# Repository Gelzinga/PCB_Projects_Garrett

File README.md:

# PCB_Projects_Garrett
Repository of PCB designs

This repository contains some of my recent PCB designs, namely an active filtering op-amp circuit for a laser tag receiver, an IOT board with onboard buck converter and external hardware support, and a low-power bluetooth remote . All designs have been done in KiCad.

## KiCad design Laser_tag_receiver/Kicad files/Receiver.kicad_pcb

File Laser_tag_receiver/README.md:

###### THIS IS THE READ ME FOR THE RECEIVER BOARD #######

This board is a receiver for a laser tag project. The circuit is built with two op-amps with active filtering. The low pass filters are implimented using a series capacitor and resistor, and the high pass filters 
with the Gain bandwidth product property of the OP-AMP. The circuit attenuates high and low noise frequencies and provides around 160 dB of gain to the desired current domain signal genererated through the photdiode. Expected noise frequencies of 100 Hz and 10k hz. Circuit provides more than enough attenuation for noise signals, around 60 dB. 

Design Choices 
1. Capacitors were placed close to the power rails in order to achieve effective stabilization of power supply. 
2. Additional low pass filter was placed on power supply to eliminate higher frequency noise directly from the power.
3. Gain bandwidth property of opamp was used for high frequency noise attenuation to reduce compenents/complexity/poles of the circuit.
4. Gain around 160 dB in order to provide a useful signal. Attenuation of expected noise signals around 60 dB down. Bode plot is included in the PCB folder.
5. Ground was made a plane to reduce noise
6. Two inverting OP-AMPS were used. More OP-AMPS could've been used to increase gain, but for lower complexity and cost just two were used. 

Debugging Process
1. Major challenge was fitting all of the components in the board. Several vias had to be used
2. LT Spice schematic was used to verify appropriate attenuation of signals.
3. Included hardware support for extra filters for more attenuation if needed. Pins were used that can be bypassed with header caps.

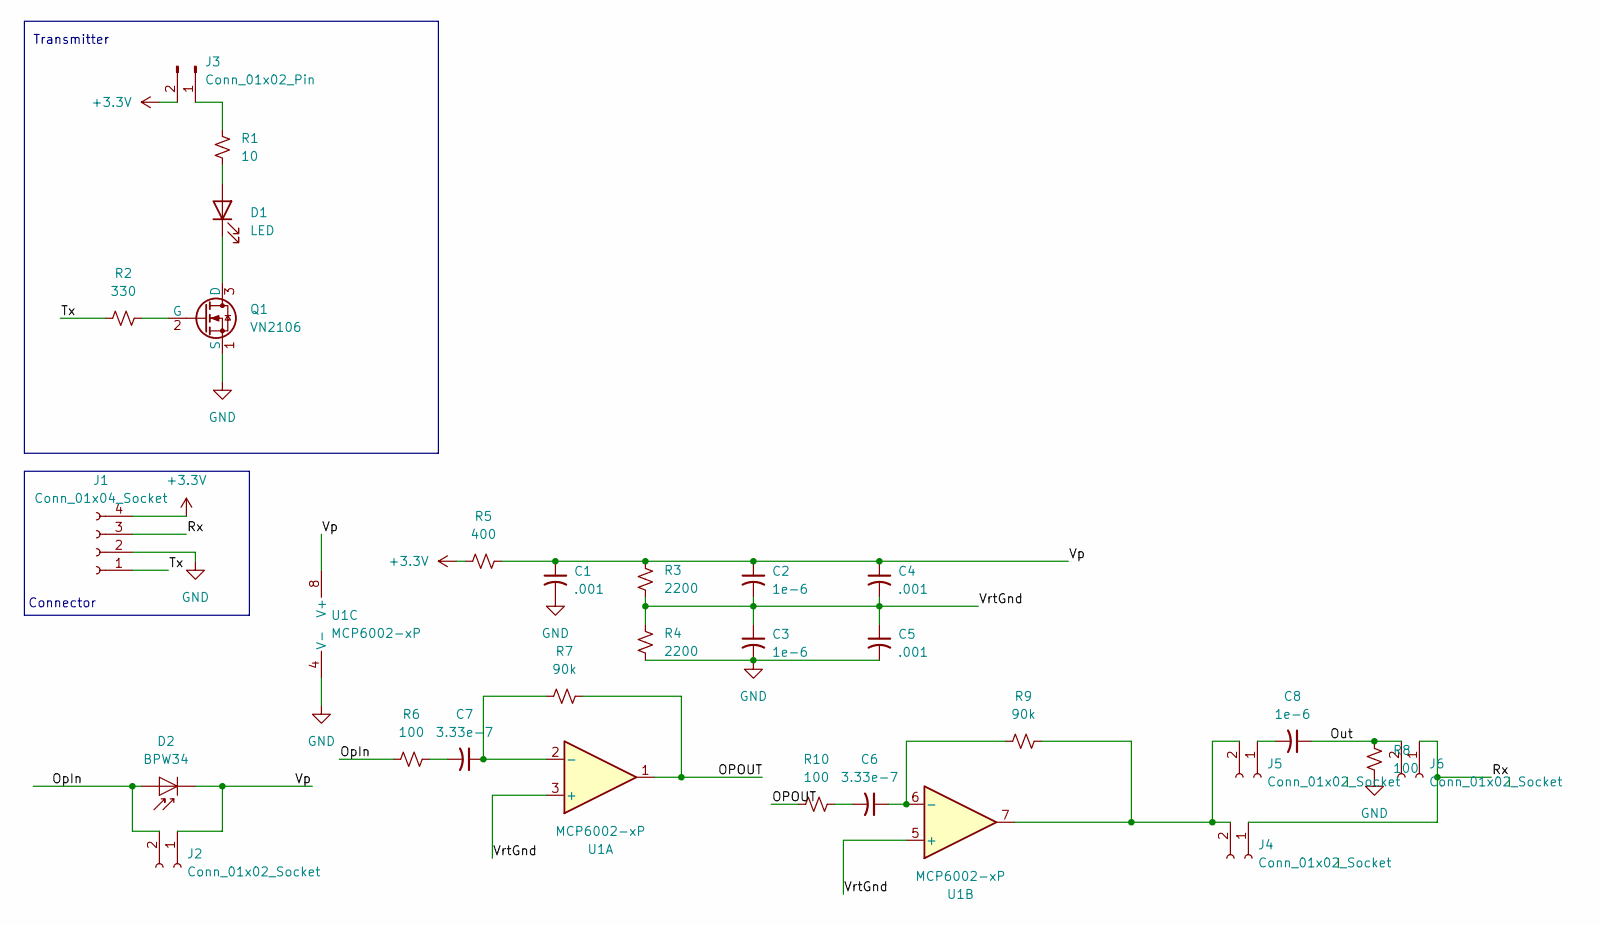
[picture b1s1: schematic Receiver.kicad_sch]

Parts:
C1, C4, C5: .001; CP_Radial_D10.0mm_P5.00mm
C2, C3, C8: 1e-6; C_Disc_D10.0mm_W2.5mm_P5.00mm
C6, C7: 3.33e-7; C_Disc_D10.0mm_W2.5mm_P5.00mm
D1: LED; LED_D3.0mm
D2: BPW34; Osram_DIL2_4.3x4.65mm_P5.08mm
J1: Conn_01x04_Socket; PinSocket_1x04_P2.54mm_Vertical
J2, J4, J5, J6: Conn_01x02_Socket; JST_PH_B2B-PH-K_1x02_P2.00mm_Vertical
J3: Conn_01x02_Pin; PinHeader_1x02_P2.54mm_Vertical
Q1: VN2106; TO-92L_Inline
R1: 10; R_Axial_DIN0207_L6.3mm_D2.5mm_P7.62mm_Horizontal
R2: 330; R_Axial_DIN0207_L6.3mm_D2.5mm_P7.62mm_Horizontal
R3, R4: 2200; R_Axial_DIN0207_L6.3mm_D2.5mm_P7.62mm_Horizontal
R5: 400; R_Axial_DIN0207_L6.3mm_D2.5mm_P7.62mm_Horizontal
R6, R8, R10: 100; R_Axial_DIN0207_L6.3mm_D2.5mm_P7.62mm_Horizontal
R7, R9: 90k; R_Axial_DIN0207_L6.3mm_D2.5mm_P7.62mm_Horizontal
U1: MCP6002-xP; DIP-8_W7.62mm

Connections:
+3.3V: J1.4, J3.2, R5.1
/OPOUT: R7.2, R10.1, U1.1
/OpIn: D2.2 (A), J2.2, R6.1
/Out: C8.1, J6.2, R8.2
/Rx: J1.3, J4.1, J6.1
/Tx: J1.1, R2.1
/Vp: C1.1, C2.1, C4.1, D2.1 (K), J2.1, R3.1, R5.2, U1.8 (V+)
/VrtGnd: C2.2, C3.1, C4.2, C5.1, R3.2, R4.1, U1.3 (+), U1.5 (+)
GND: C1.2, C3.2, C5.2, J1.2, Q1.1 (S), R4.2, R8.1, U1.4 (V-)
unnamed: C6.2, R10.2
unnamed: C7.2, R6.2
unnamed: D1.2 (A), R1.2
unnamed: D1.1 (K), Q1.3 (D)
unnamed: J3.1, R1.1
unnamed: J4.2, J5.2, R9.2, U1.7
unnamed: C8.2, J5.1
unnamed: Q1.2 (G), R2.2
unnamed: C7.1, R7.1, U1.2 (-)
unnamed: C6.1, R9.1, U1.6 (-)

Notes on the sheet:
Transmitter
Connector

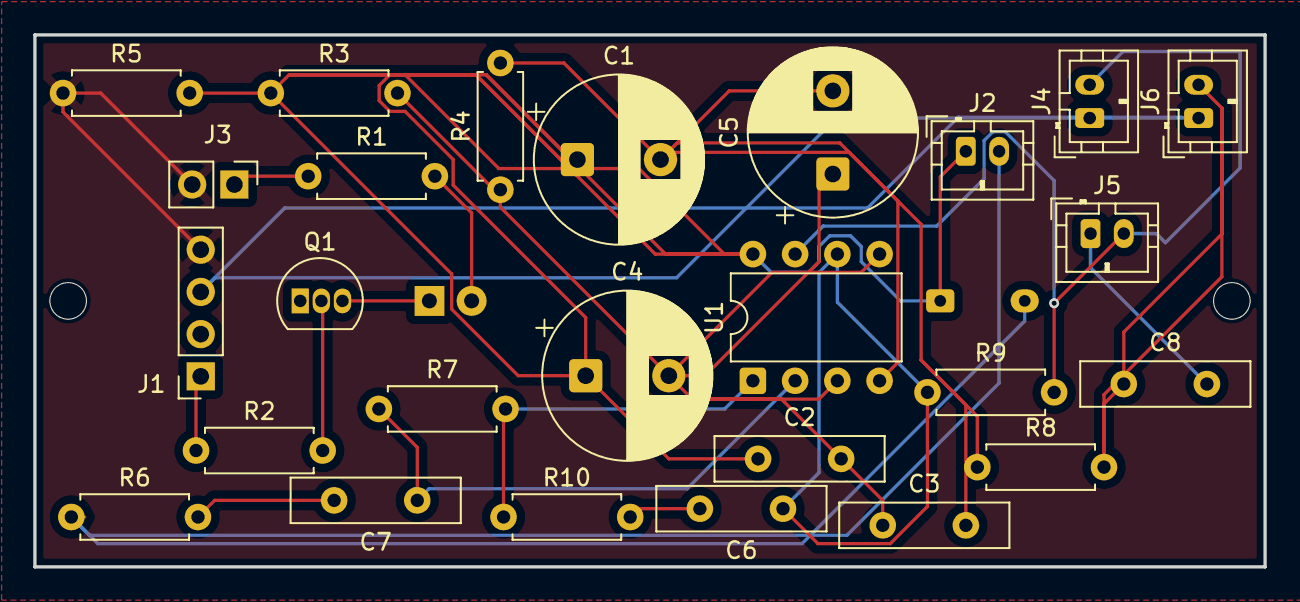
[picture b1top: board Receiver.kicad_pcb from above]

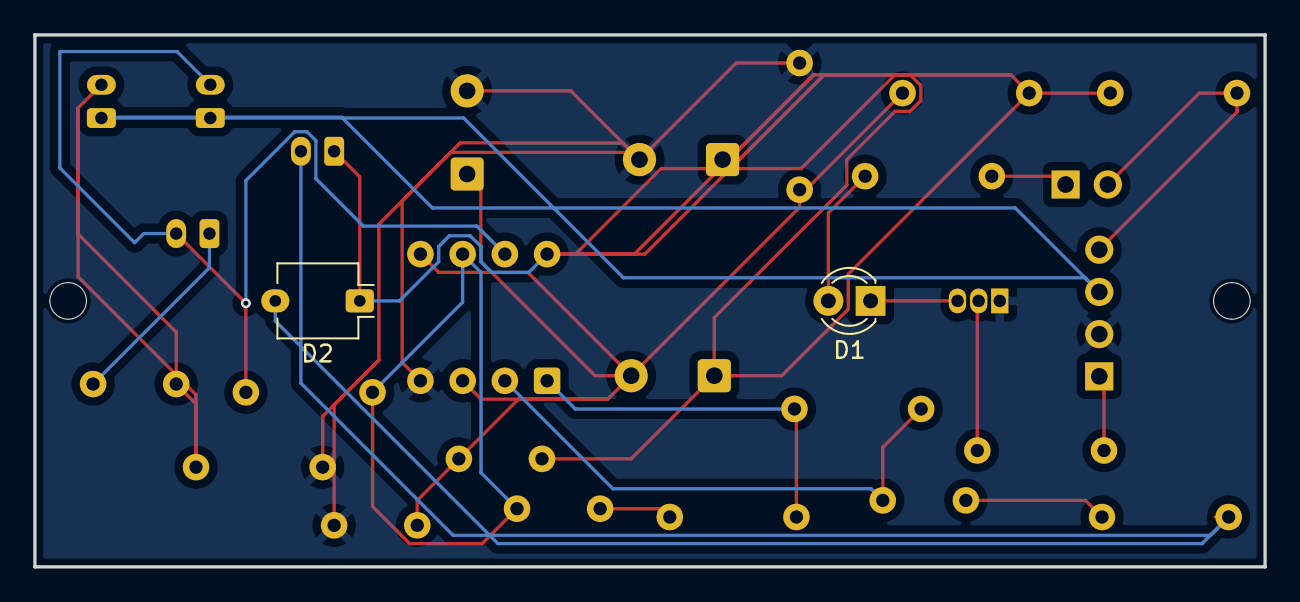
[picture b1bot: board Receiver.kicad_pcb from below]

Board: 2 copper layers, 74.0 x 32.0 mm, 28 parts (2 on the bottom side), 19 nets.

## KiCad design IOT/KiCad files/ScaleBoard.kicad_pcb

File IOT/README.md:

#### THIS IS THE READ ME FILE FOR THE IOT BOARD #####

In this folder you will find 

- Schematics 
- PCB pictures 
- KiCad files

Motivation for this board: 
This board is designed as a custom IOT device to read a digital output from a load cell ( Analog values already converted using off-board PCB) and display the value on a screen, 
indicating that more or less ingredients from the recipe sent from phone to the esp32 need to be included. Will make cooking easier and more convenient. 

Design Decisions: 
1. Multiple decoupling capacitors, each with different values to block low high, low and midband frequency noise. Decoupling capacitors were placed at several stages, but most noteably the raw input from the power supply.
2. Decoupling capacitors were placed close to the power/ground pins that they are connected to in order to further reduce noise (low noise is an absolute esssential, as the power supply must be  extremely stable
to get accurate readings from the load cell).
3. Buck converter was implimented to convert the 5v to 3.3v. The converter holds the voltage at .8 V at FB pin, so a resistor divider with high value resistors (to reduce power loss) was used. Values of 312.5k  and 100k achieve necessary 3.3v.
5. Ground was implimented as a plane to reduce potential sources of noise
6. Hardware support for a button was added, using an external pull up resistor for clarity as well as clean design. Large R values to reduce current power consumption 
7. Hardware support for SPI screen was included as well, to display the scale readings/progress.

Debugging process: 
1. Appropriate spacing to ensure proximity of capacitors to rails while still allowing for reasonable space for soldering and placement was a major problem.It required moving traces and footprints around, implimenting vias and using traces on both sides.
2. ESP 32 S3 footprint straight from the library had some vias that were .2 mm, changed to .3 mm for fabrication plausability/compatibility
3. Buck converter comes as an SMD, so this complicated things as either vias had to be made or priority for top-side traces.
4. Resistors were changed from SMD to THT for prototyping and less complexity/crowded traces on the front side. SMD technology to be explored in later iterations.

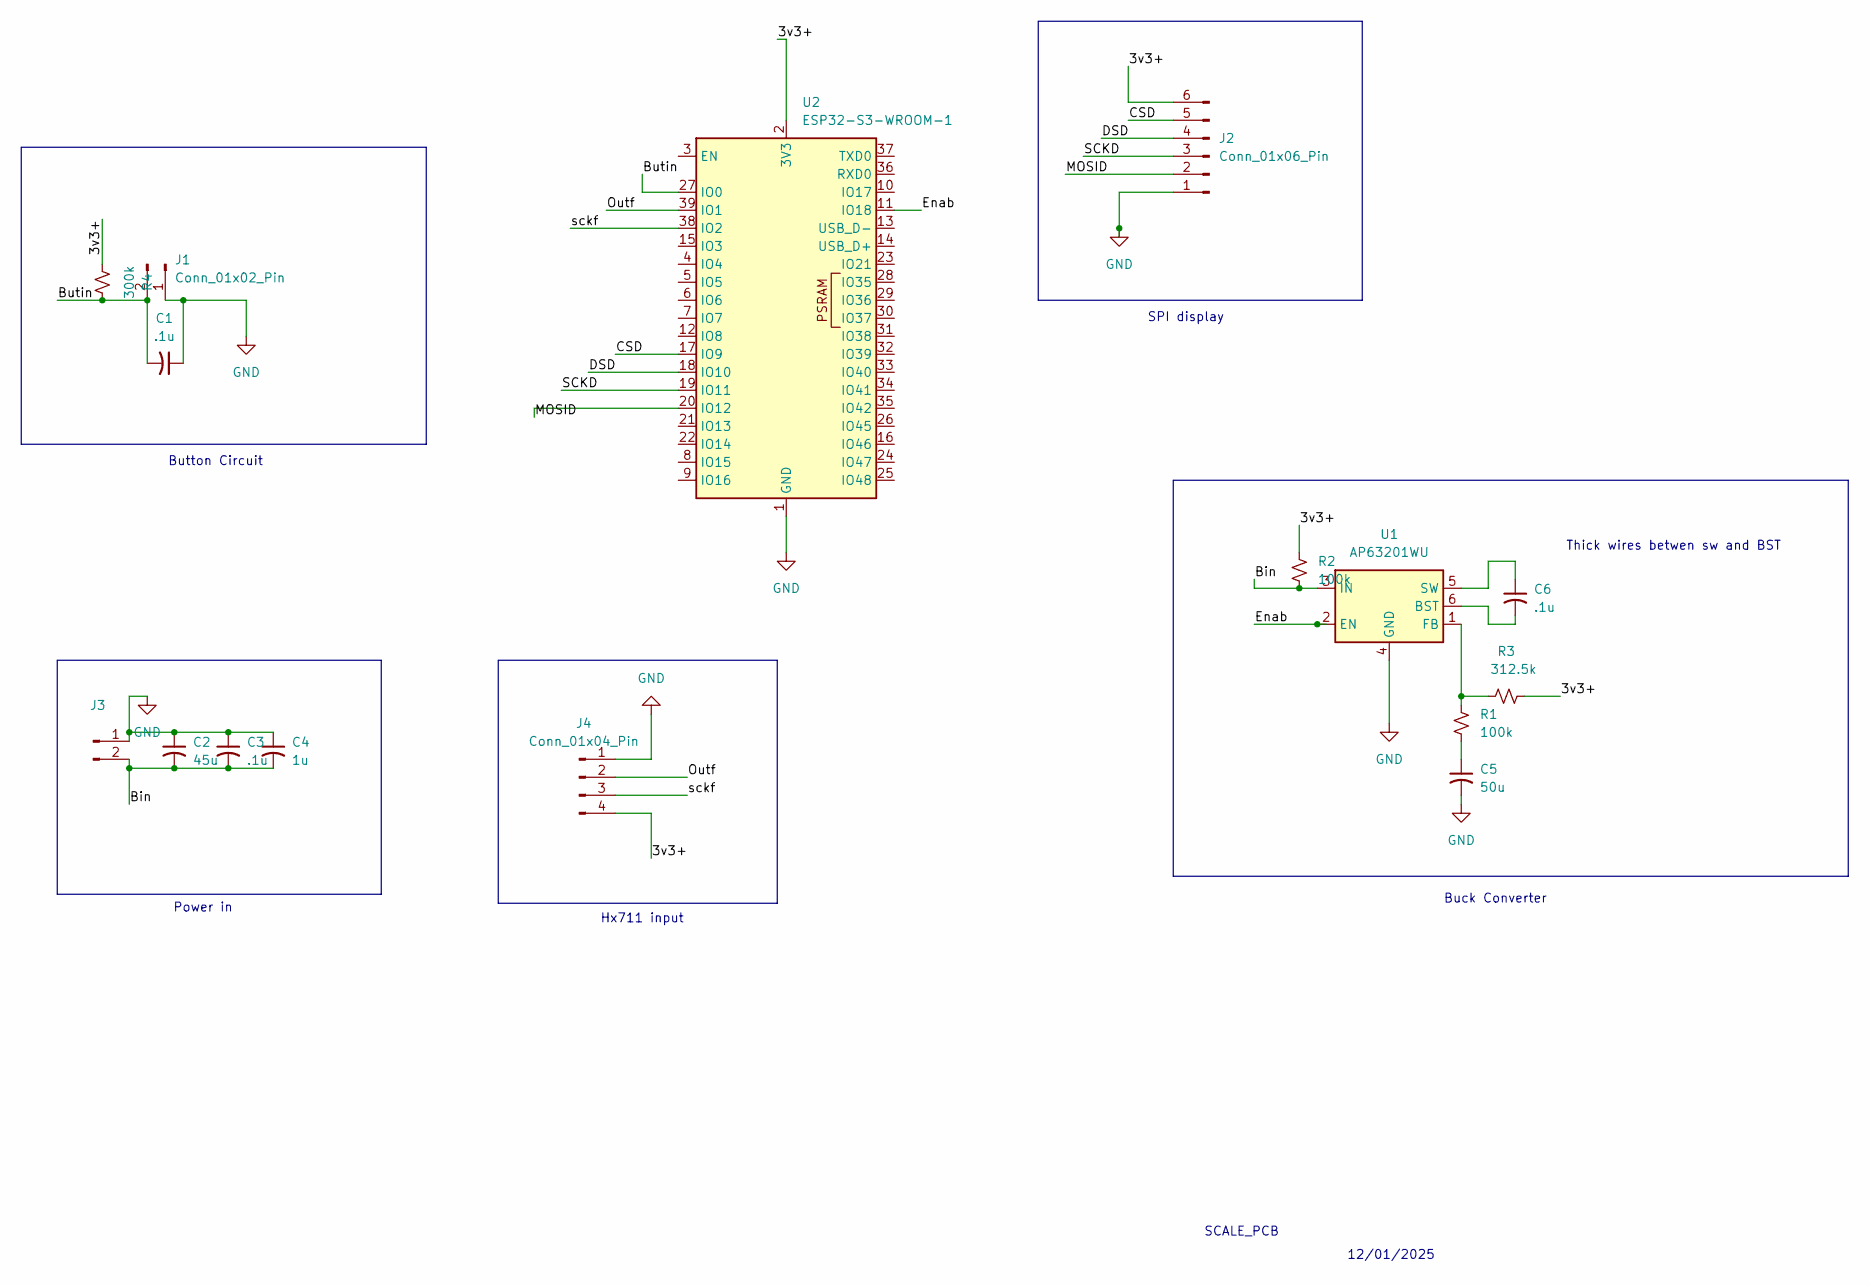
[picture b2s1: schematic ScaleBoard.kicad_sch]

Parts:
C1, C3, C6: .1u; C_Disc_D5.1mm_W3.2mm_P5.00mm
C2: 45u; C_Disc_D5.1mm_W3.2mm_P5.00mm
C4: 1u; C_Disc_D5.1mm_W3.2mm_P5.00mm
C5: 50u; C_Disc_D5.1mm_W3.2mm_P5.00mm
J1, J3: Conn_01x02_Pin; PinHeader_1x02_P2.54mm_Vertical
J2: Conn_01x06_Pin; PinHeader_1x06_P2.54mm_Vertical
J4: Conn_01x04_Pin; PinHeader_1x04_P2.54mm_Vertical
R1, R2: 100k; R_Axial_DIN0207_L6.3mm_D2.5mm_P7.62mm_Horizontal
R3: 312.5k; R_Axial_DIN0207_L6.3mm_D2.5mm_P7.62mm_Horizontal
R4: 300k; R_Axial_DIN0207_L6.3mm_D2.5mm_P7.62mm_Horizontal
U1: AP63201WU; TSOT-23-6
U2: ESP32-S3-WROOM-1

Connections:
/3v3+: J2.6, J4.4, R2.1, R3.2, R4.1, U2.2 (3V3)
/Bin: C2.2, C3.2, C4.2, J3.2, R2.2, U1.3 (IN)
/Butin: C1.2, J1.2, R4.2, U2.27 (IO0)
/CSD: J2.5, U2.17 (IO9)
/DSD: J2.4, U2.18 (IO10)
/Enab: U1.2 (EN), U2.11 (IO18)
/MOSID: J2.2, U2.20 (IO12)
/Outf: J4.2, U2.39 (IO1)
/SCKD: J2.3, U2.19 (IO11)
/sckf: J4.3, U2.38 (IO2)
GND: C1.1, C2.1, C3.1, C4.1, C5.2, J1.1, J2.1, J3.1, J4.1, U1.4 (GND), U2.1 (GND), U2.40 (GND), U2.41 (GND)
unnamed: C5.1, R1.2
unnamed: C6.2, U1.6 (BST)
unnamed: R1.1, R3.1, U1.1 (FB)
unnamed: C6.1, U1.5 (SW)

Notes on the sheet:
12/01/2025
SPI display
Buck Converter
SCALE_PCB
Button Circuit
Thick wires betwen sw and BST
Power in
Hx711 input

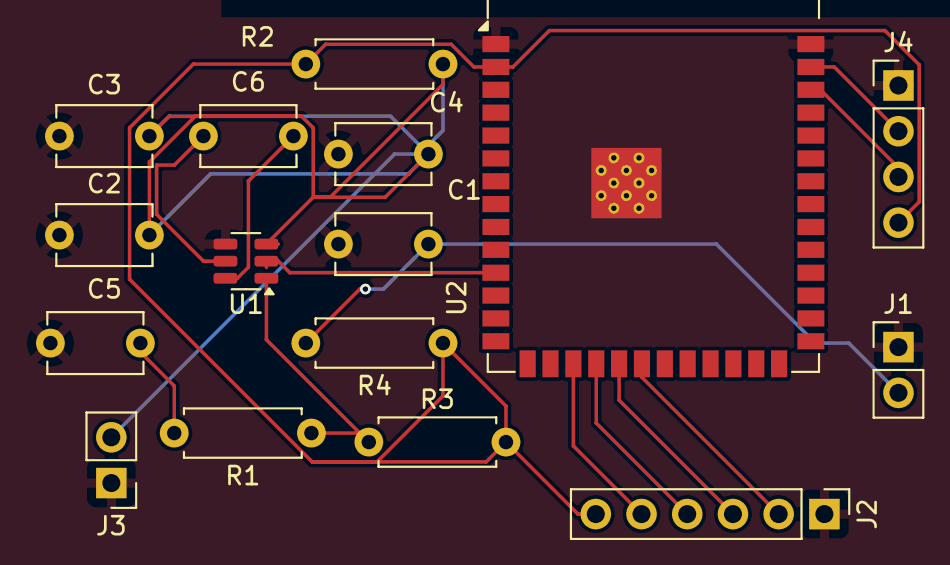
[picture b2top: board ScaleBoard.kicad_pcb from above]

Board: 2 copper layers, 16 parts (0 on the bottom side), 15 nets.

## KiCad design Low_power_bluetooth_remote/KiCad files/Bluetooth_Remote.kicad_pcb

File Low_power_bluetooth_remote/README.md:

# Bluetooth Remote Controller (ESP32)

## Overview
This project is a **low-power Bluetooth remote controller** using an ESP32-S3 MCU.  
It supports multiple buttons for controlling music playback and other Bluetooth HID commands. The design focuses on **low sleep current, clean grounding, proper power design, and reliable input handling**.  

The goal is not just a working remote, but a **portfolio-quality PCB demonstrating best practices in embedded hardware design**.

---

## Features

- ESP32-S3-WROOM-1 MCU (supports Bluetooth Low Energy)
- Up to 4 buttons (Bin1–Bin4)
- USB-C for power and programming
- Low dropout regulator for 3.3 V power supply
- Decoupling capacitors near power pins
- RC filters for buttons to suppress EMI
- Designed for low sleep current (<10 µA target)
- Clean ground plane with controlled high-current loops
- Optional LED indicators for button press feedback
- 2-layer PCB, designed for manufacturability

---

## Design Decisions

### 1. Power Design
- **Input:** USB 5 V  
- **Voltage Regulation:** AP63201 buck converter provides 3.3 V for MCU and peripherals.  
- **Decoupling:** 0.1–1 µF capacitors placed directly at power pins to reduce switching noise.  
- **Battery Support:** Li-ion support via MCP73831 charge IC (optional for standalone use).  
- **Sleep Current Optimization:** 
  - All unused GPIOs set to avoid floating
  - LEDs can be disabled in firmware during deep sleep
  - Low quiescent current regulator chosen

---

### 2. Button Inputs and Debouncing
- **Pull-ups:** Internal MCU pull-ups used where possible  
- **RC Filtering:** Small capacitors (~0.01–0.1 µF) added to buttons to suppress EMI and reduce bounce noise  
- **Software Debounce:** Firmware ensures a 20–50 ms stable input before registering a button press  
- **Routing:** Button traces kept short and away from high-current paths and SW nodes of the buck converter

---

### 3. Grounding Strategy
- **Solid Ground Plane:** Entire board uses a continuous GND plane for digital and analog return paths  
- **High-current Loops:** Buck converter input/output loop minimized to reduce noise  
- **Button and GPIO Routing:** Kept away from noisy nodes (SW, inductor) and antenna to preserve signal integrity

---

### 4. MCU & Connectivity
- **ESP32-S3-WROOM-1:** Chosen for BLE support, low-power sleep modes, and sufficient GPIO for multiple buttons  
- **UART Header:** Exposed for programming and debugging (J6)  
- **GPIO Mapping:** Each button connected to a dedicated GPIO pin (Bin1–Bin4) with pull-up resistor

---

### 5. PCB Layout Notes
- **Layering:** 2-layer PCB with top and bottom copper, ground plane on bottom  
- **Component Placement:** 
  - Decoupling capacitors close to MCU power pins
  - Buck converter and input capacitors placed to minimize high-di/dt loop area  
- **Antenna Clearance:** Kept area around ESP32 antenna free from copper to maximize RF performance  
- **Vias:** Used to connect top and bottom planes for GND continuity

---

## Files Included

- `schematics/` — KiCad schematic PDF and source file  
- `pcb/` — PCB layout images and 3D renders  
- `manufacturing/` — Gerbers, drill files, BOM (CSV)  

---

## Future Enhancements
- Battery-powered operation with Li-ion charging
- LED status indicators for battery and Bluetooth connection
- Expansion to additional buttons or rotary encoder
- Firmware implementing Bluetooth HID standard for multiple platforms

---

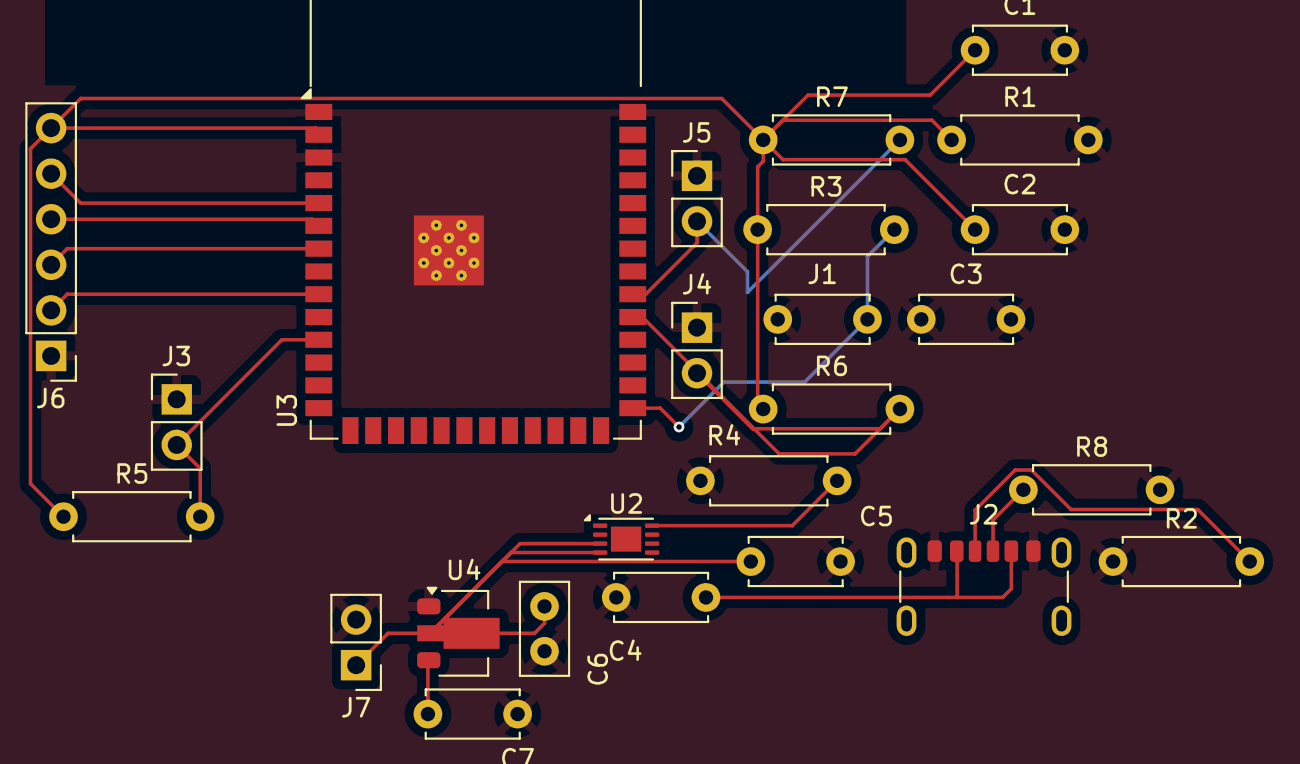
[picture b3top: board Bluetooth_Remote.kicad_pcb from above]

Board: 2 copper layers, 25 parts (0 on the bottom side), 16 nets.

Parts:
C1, C3: .1u; C_Disc_D5.0mm_W2.5mm_P5.00mm
C2: 10u; C_Disc_D5.0mm_W2.5mm_P5.00mm
C4, C5, C7: 1u; C_Disc_D5.0mm_W2.5mm_P5.00mm
C6: 1u; C_Disc_D5.0mm_W2.5mm_P2.50mm
J1: Conn_01x02_Pin; C_Disc_D5.0mm_W2.5mm_P5.00mm
J2: USB_C_Receptacle_USB2.0_14P; USB_C_Receptacle_GCT_USB4125-xx-x-0190_6P_TopMnt_Horizontal
J3, J4, J5, J7: Conn_01x02_Pin; PinHeader_1x02_P2.54mm_Vertical
J6: Uart header; PinHeader_1x06_P2.54mm_Vertical
R1: 1M; R_Axial_DIN0207_L6.3mm_D2.5mm_P7.62mm_Horizontal
R2, R8: 5.1k; R_Axial_DIN0207_L6.3mm_D2.5mm_P7.62mm_Horizontal
R3, R5, R6, R7: 100k; R_Axial_DIN0207_L6.3mm_D2.5mm_P7.62mm_Horizontal
R4: 4.7k; R_Axial_DIN0207_L6.3mm_D2.5mm_P7.62mm_Horizontal
U2: MCP73831-2-MC; DFN-8-1EP_3x2mm_P0.5mm_EP1.7x1.4mm
U3: ESP32-S3-WROOM-1
U4: MCP1700x-120xxMB; SOT-89-3

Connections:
/3v3: C1.1, C2.1, J6.6, R1.1, R3.1, R5.1, R6.1, R7.1, U3.2 (3V3)
/BAT+: C5.1, C6.2, J7.1, U2.3 (V_{BAT}), U2.4 (V_{BAT}), U4.2 (VI)
/Bin: J1.2, R3.2, U3.27 (IO0)
/Bin2: J3.2, R5.2, U3.11 (IO18)
/Bin3: J4.2, R6.2, U3.31 (IO38)
/Bin4: J5.2, R7.2, U3.32 (IO39)
/En: J6.4, U3.6 (IO6)
/GPIO1: J6.5, U3.5 (IO5)
/Rx: J6.3, U3.7 (IO7)
/Tx: J6.2, U3.9 (IO16)
/VDD: C4.2, J2.A9 (VBUS), J2.B9 (VBUS), U2.1 (V_{DD}), U2.2 (V_{DD})
GND: C1.2, C2.2, C3.1, C3.2, C4.1, C5.2, C6.1, C7.2, J1.1, J2.A12 (GND), J2.B12 (GND), J3.1, J4.1, J5.1, J6.1, J7.2, R1.2, R2.1, R4.1, R8.2, U2.6 (V_{SS}), U3.1 (GND), U3.3 (EN), U3.40 (GND), U3.41 (GND), U4.1 (GND)
unnamed: J2.A5 (CC1), R2.2
unnamed: J2.B5 (CC2), R8.1
unnamed: R4.2, U2.8 (PROG)
unnamed: C7.1, U4.3 (VO)

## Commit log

2025-12-24 Update README with project descriptions
    Added a brief description of the PCB designs in the repository.
2025-12-24 Create IOT_board
2025-12-24 added the necessary folders and screenshots for scale IOT project as well as the receiver circuit
2025-12-24 Add README for laser tag receiver board
    Added detailed documentation for the receiver board, including design choices and debugging process.
2025-12-24 Update README with debugging process details
    Added details about hardware support for extra filters.
2025-12-24 Update README with noise frequency and attenuation info
    Added expected noise frequencies and attenuation details.
2025-12-25 added in the files for the Bluetooth remote
2025-12-25 Create README.md for Bluetooth remote controller
    Added detailed README for Bluetooth remote controller project.
2025-12-25 Update README with new PCB design details
    Added a low-power bluetooth remote to the project description.
